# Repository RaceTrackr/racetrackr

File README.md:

# racetrackr
A repository for the student-led development of Racetrackr - An asset used for tracking data, both in the pits and on raceday at greenpower racing events.
This repository is happy for any help you are willing to give :)

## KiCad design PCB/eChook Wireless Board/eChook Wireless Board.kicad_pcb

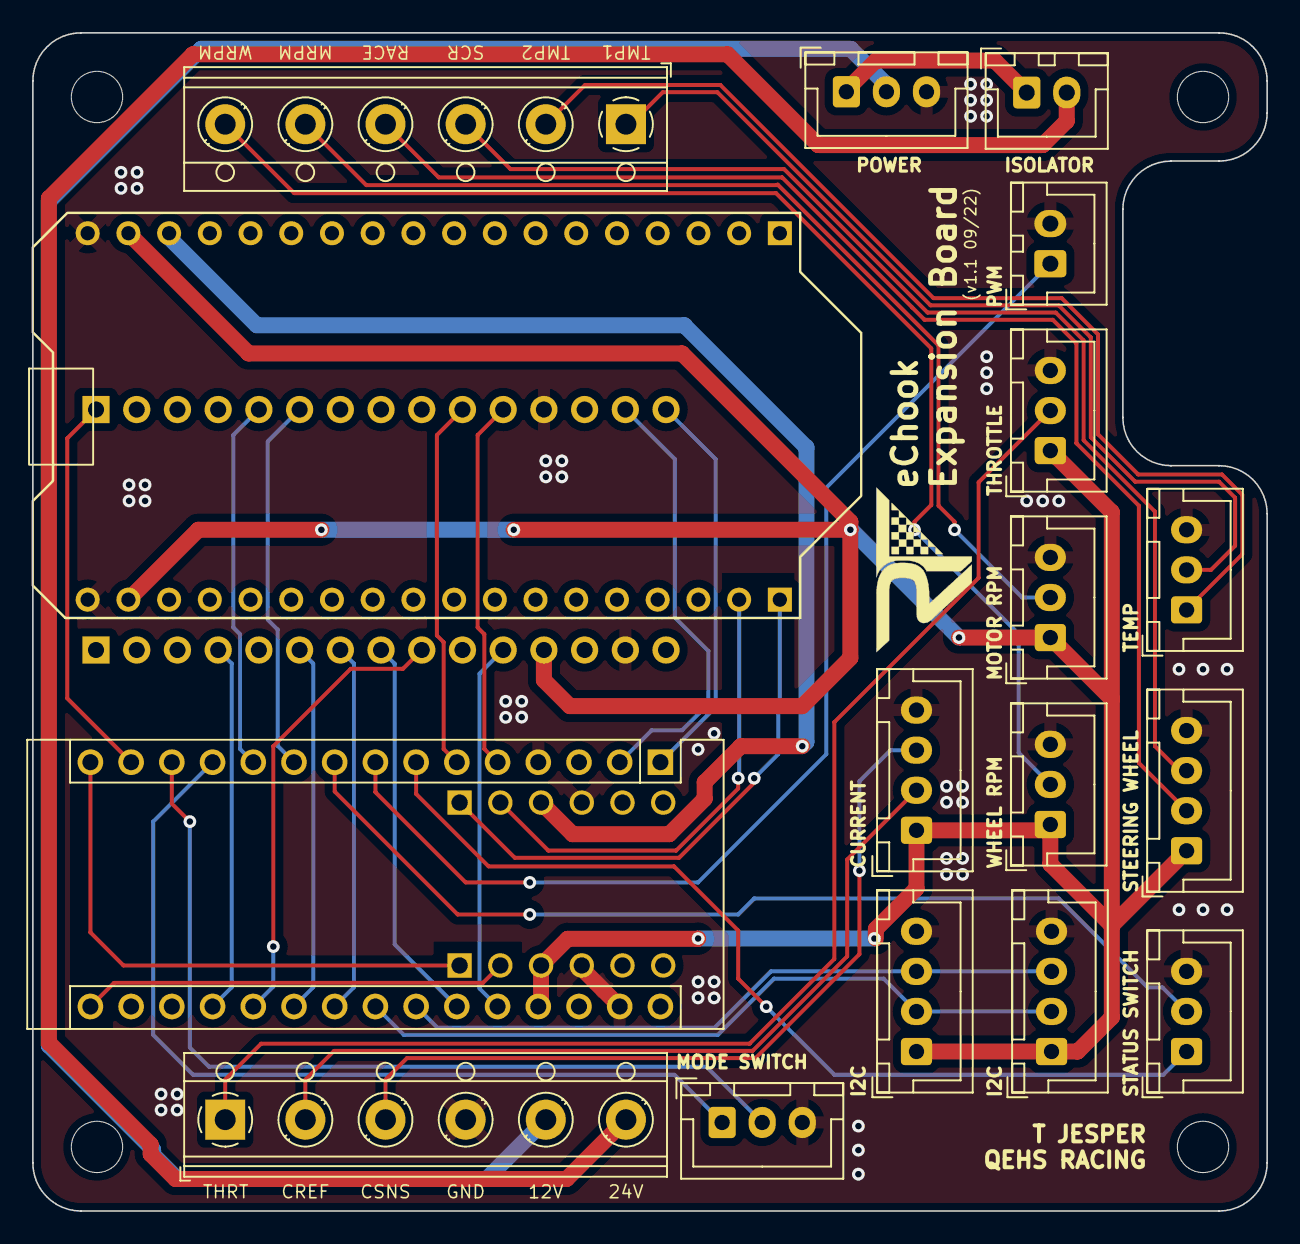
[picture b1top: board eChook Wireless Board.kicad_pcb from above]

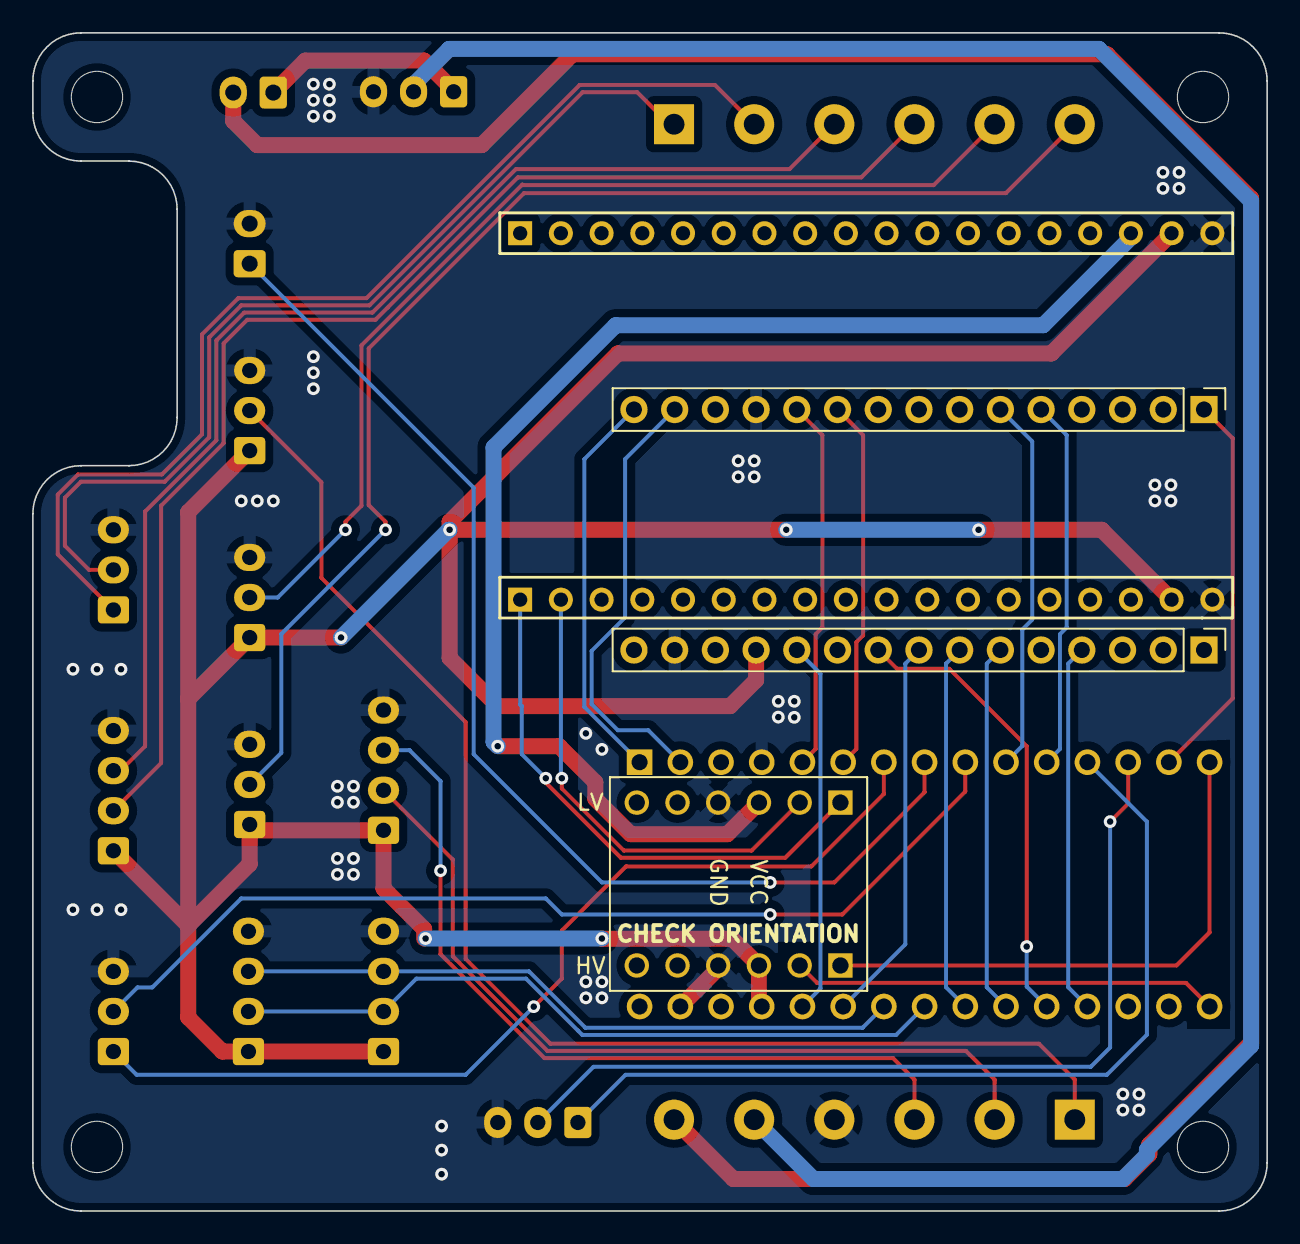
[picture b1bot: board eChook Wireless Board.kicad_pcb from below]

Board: 2 copper layers, 77.0 x 73.5 mm, 24 parts (3 on the bottom side), 39 nets.

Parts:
A: MountingHole_3.2mm_M3
A1: Arduino_Nano_v3.x; Arduino_Nano
B: MountingHole_3.2mm_M3
C: MountingHole_3.2mm_M3
D: MountingHole_3.2mm_M3
J1: POWER_CONNECTION; JST_XH_B3B-XH-A_1x03_P2.50mm_Vertical
J2: POWER_SWITCH; JST_XH_B2B-XH-A_1x02_P2.50mm_Vertical
J3: PWM_OUTPUT_CONN; JST_XH_B2B-XH-A_1x02_P2.50mm_Vertical
J4, J7: Conn_01x15_Male; PinHeader_1x15_P2.54mm_Vertical
J5: THROTTLE_CONNECTION; JST_XH_B3B-XH-A_1x03_P2.50mm_Vertical
J6: I2C_1_CONN; JST_XH_B4B-XH-A_1x04_P2.50mm_Vertical
J8: I2C_2_CONN; JST_XH_B4B-XH-A_1x04_P2.50mm_Vertical
J9: MOTOR_RPM_CONNECTION; JST_XH_B3B-XH-A_1x03_P2.50mm_Vertical
J10: WHEEL_RPM_CONNECTION; JST_XH_B3B-XH-A_1x03_P2.50mm_Vertical
J12, J18: STATUS_CONNECTION; JST_XH_B3B-XH-A_1x03_P2.50mm_Vertical
J13: CURRENT_CONN; JST_XH_B4B-XH-A_1x04_P2.50mm_Vertical
J14: TEMP_CONNECTION; JST_XH_B3B-XH-A_1x03_P2.50mm_Vertical
J15: WHEEL_CONN; JST_XH_B4B-XH-A_1x04_P2.50mm_Vertical
J16, J17: Screw_Terminal_01x06; TerminalBlock_RND_205-00016_1x06_P5.00mm_Horizontal
U1: LogicLevelConverter; CONV_BOB-12009
U2: ESP32_LoRa; ESP32 LoRa

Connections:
12_B2B: J1.2, J16.5
24_B2B: J2.2, J16.6
+3V3: U1.LV, U2.16 (3V3)
+5V: A1.27 (+5V), J4.12, J5.1, J6.1, J8.1, J9.1, J10.1, J13.1, J15.1, U1.HV, U2.17 (5V), U2.20 (5V)
/+24V_ISOLATED: J1.1, J2.1
BATT_1: A1.26 (A7), J4.11
BATT_T: A1.19 (A0), J4.4
BRAKE: A1.10 (D7), J7.6
BT_IN: A1.2 (D0/RX), J7.14
BT_OUT: A1.1 (D1/TX), J7.15
CREF_B2B: J13.2, J16.2
CSENSE_B2B: J13.3, J16.3
CURRENT: A1.21 (A2), J4.6
GND: A1.4 (GND), A1.29 (GND), J1.3, J3.2, J4.14, J5.3, J6.4, J7.12, J8.4, J9.3, J10.3, J12.3, J13.4, J14.3, J15.4, J16.4, J18.3, U1.GND_1 (GND), U1.GND_2 (GND), U2.18 (GND), U2.19 (GND)
MODE_INPUT_1: A1.12 (D9), J18.1
MODE_INPUT_2: A1.13 (D10), J18.2
MOTOR_PWM: A1.8 (D5), J3.1
MOTOR_RPM: A1.5 (D2), J7.11
MRPM_B2B: J9.2, J17.5
RACE_START: A1.11 (D8), J7.5
RACE_START_B2B: J15.2, J17.4
RACE_SWITCH: A1.7 (D4), J12.1
RX_HIGH: A1.16 (D13), U1.HV2
RX_LOW: U1.LV1, U2.36 (GPIO16)
SCL: A1.24 (A5), J6.3, J8.3
SCREEN_SWITCH: A1.14 (D11), J7.1
SCREEN_SWITCH_B2B: J15.3, J17.3
SDA: A1.23 (A4), J6.2, J8.2
TELEMETRY_SWITCH: A1.9 (D6), J12.2
TEMP1_B2B: J14.1, J17.2
TEMP2_B2B: J14.2, J17.1
TEMP_1: A1.20 (A1), J4.9
TEMP_2: A1.25 (A6), J4.8
THROTTLE: A1.22 (A3), J4.7
THROTTLE_B2B: J5.2, J16.1
TX_HIGH: A1.15 (D12), U1.HV1
TX_LOW: U1.LV2, U2.35 (GPIO17)
WHEEL_RPM: A1.6 (D3), J7.10
WRPM_B2B: J10.2, J17.6

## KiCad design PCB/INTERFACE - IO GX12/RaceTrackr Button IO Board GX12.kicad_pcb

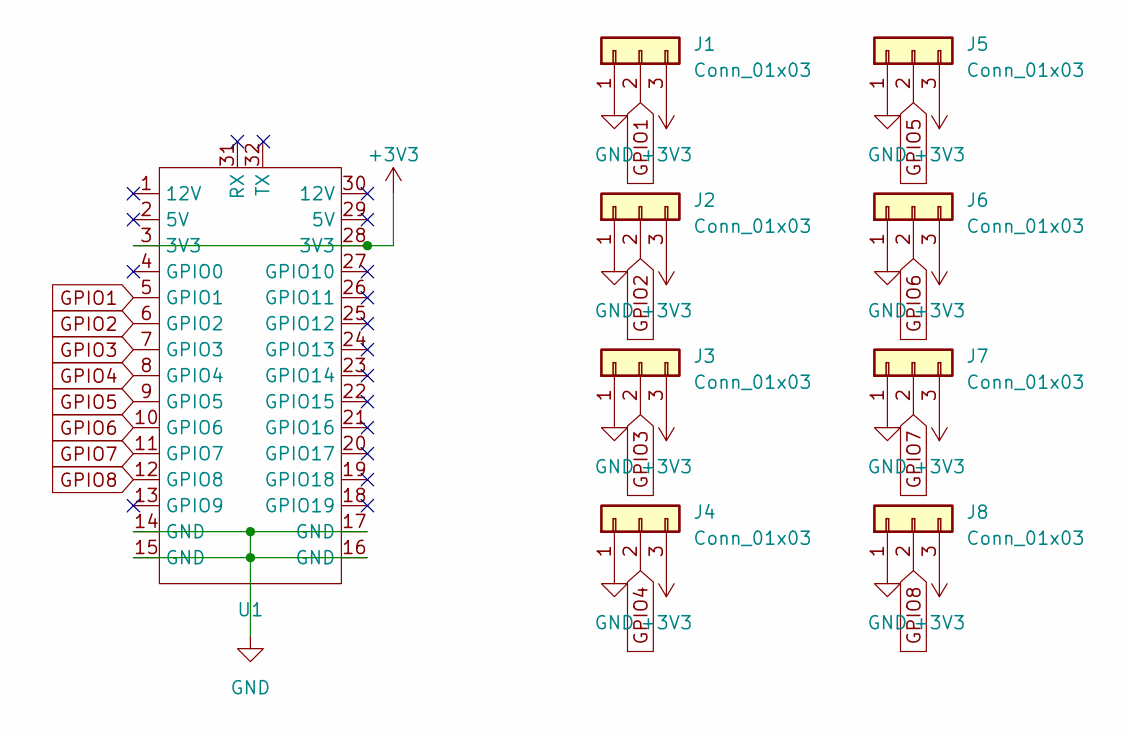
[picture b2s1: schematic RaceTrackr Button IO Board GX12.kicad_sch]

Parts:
J1, J2, J3, J4, J5, J6, J7, J8: Conn_01x03; GX12-3
U1: RaceTrackr Interface Board Reference

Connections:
+3V3: J1.3, J2.3, J3.3, J4.3, J5.3, J6.3, J7.3, J8.3, U1.3 (3V3), U1.28 (3V3)
GND: J1.1, J2.1, J3.1, J4.1, J5.1, J6.1, J7.1, J8.1, U1.14 (GND), U1.15 (GND), U1.16 (GND), U1.17 (GND)
GPIO1: J1.2, U1.5 (GPIO1)
GPIO2: J2.2, U1.6 (GPIO2)
GPIO3: J3.2, U1.7 (GPIO3)
GPIO4: J4.2, U1.8 (GPIO4)
GPIO5: J5.2, U1.9 (GPIO5)
GPIO6: J6.2, U1.10 (GPIO6)
GPIO7: J7.2, U1.11 (GPIO7)
GPIO8: J8.2, U1.12 (GPIO8)

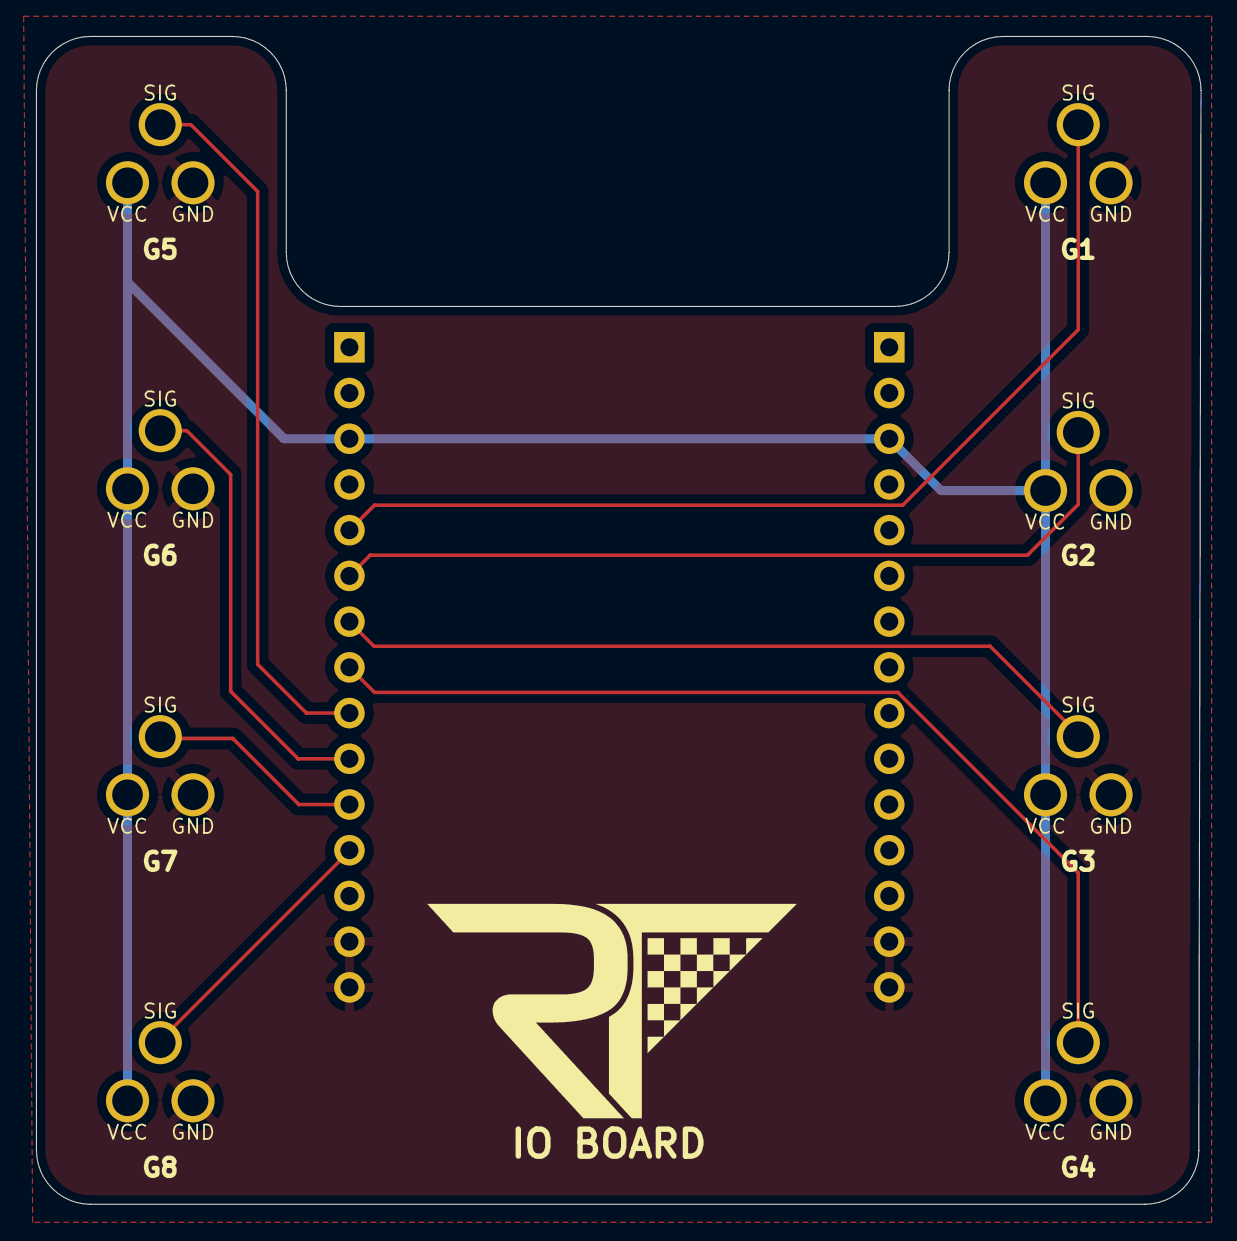
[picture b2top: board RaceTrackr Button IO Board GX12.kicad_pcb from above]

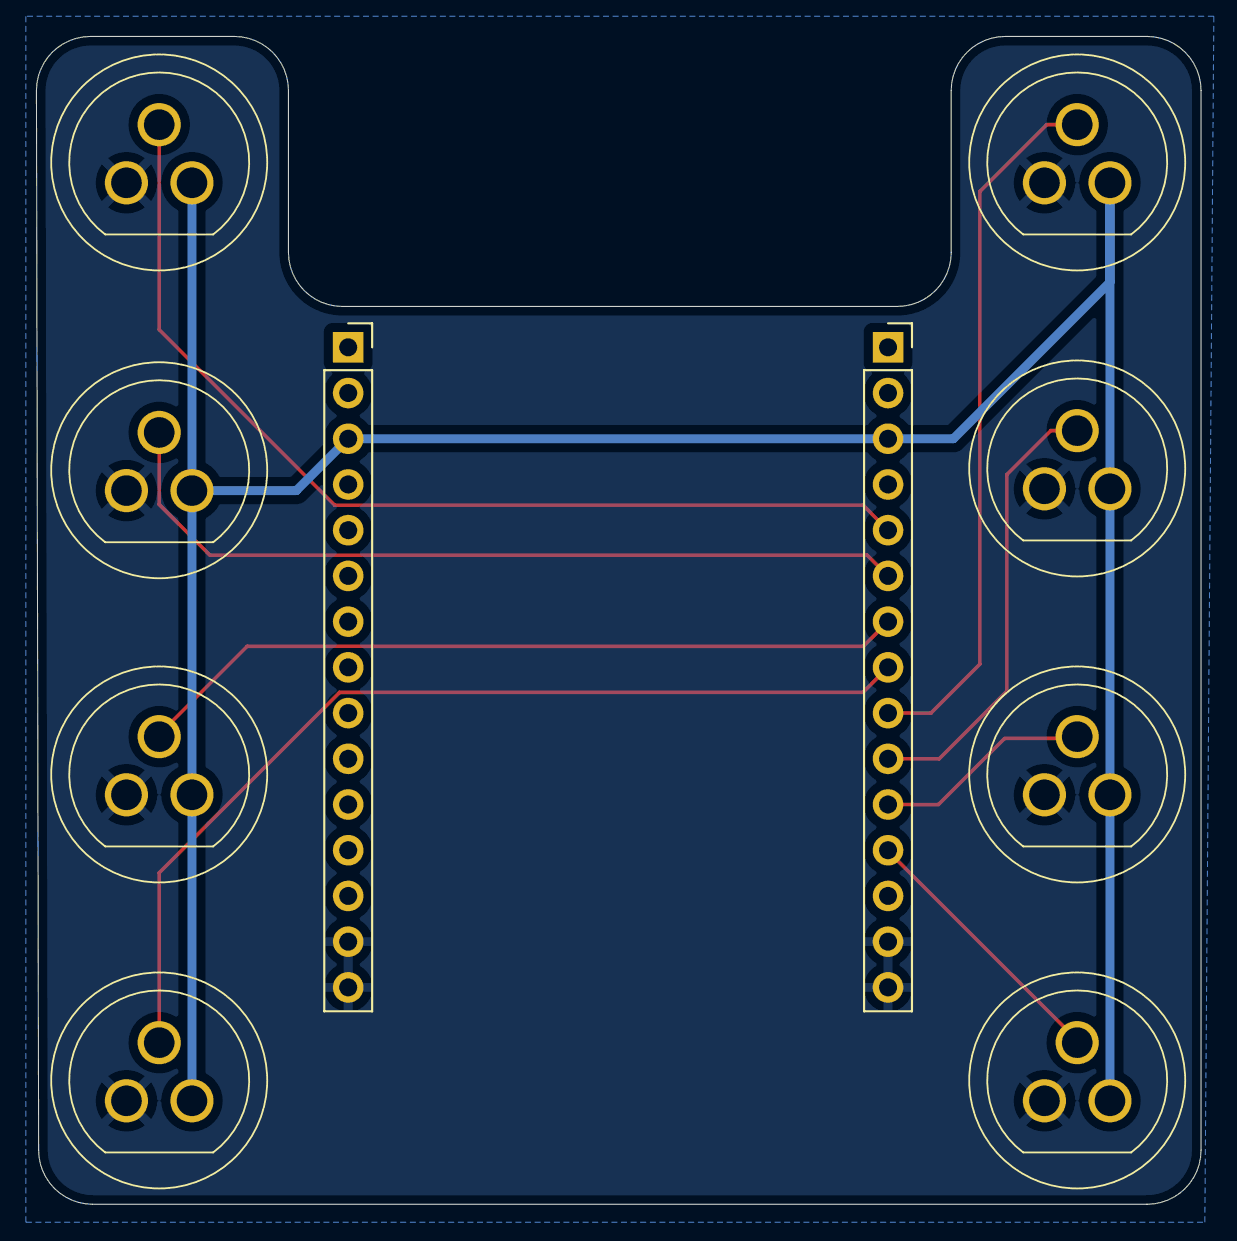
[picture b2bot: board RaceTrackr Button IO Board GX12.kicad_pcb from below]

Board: 2 copper layers, 64.7 x 64.9 mm, 9 parts (8 on the bottom side), 10 nets.

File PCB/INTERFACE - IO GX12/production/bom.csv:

Designator,Footprint,Quantity,Value,LCSC Part #
"J1, J2, J3, J4, J5, J6, J7, J8",GX12-3_NOSS,8,Conn_01x03,
U1,RaceTrackr Interface Board Reference,1,~,

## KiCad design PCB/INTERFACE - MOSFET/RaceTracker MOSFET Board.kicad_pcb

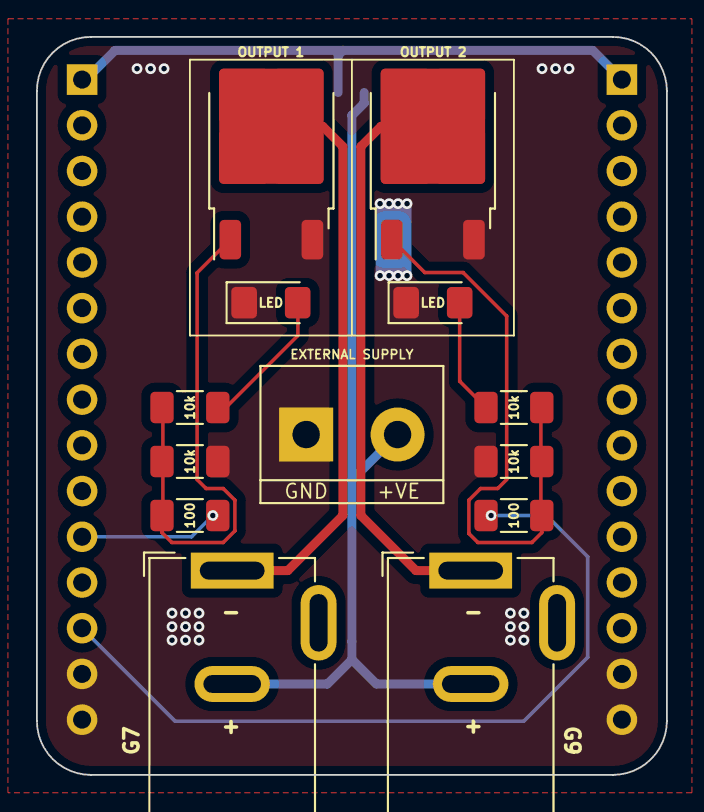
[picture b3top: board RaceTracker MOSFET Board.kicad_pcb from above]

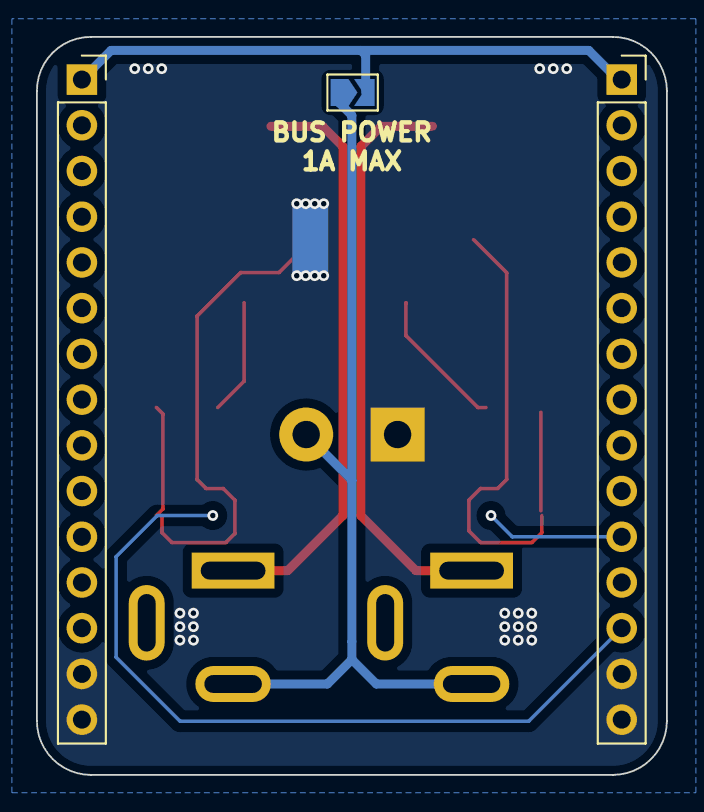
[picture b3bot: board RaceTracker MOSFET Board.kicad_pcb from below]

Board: 2 copper layers, 35.0 x 41.0 mm, 16 parts (3 on the bottom side), 13 nets.

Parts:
BUS POWER: BUS POWER; SolderJumper-2_P1.3mm_Open_TrianglePad1.0x1.5mm
D1, D2: LED; LED_1206_3216Metric_Pad1.42x1.75mm_HandSolder
J1: CON_L; PinSocket_1x15_P2.54mm_Vertical
J2: CON_R; PinSocket_1x15_P2.54mm_Vertical
J3: DC IN; TerminalBlock_bornier-2_P5.08mm
J6: OUTPUT 1; BarrelJack_GCT_DCJ200-10-A_Horizontal
J7: OUTPUT 2; BarrelJack_GCT_DCJ200-10-A_Horizontal
OUTPUT 1, OUTPUT 2: IRF540N; TO-252-2
R1, R4: 100; R_1206_3216Metric_Pad1.30x1.75mm_HandSolder
R2, R3, R5, R6: 10k; R_1206_3216Metric_Pad1.30x1.75mm_HandSolder

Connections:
+3V3: J1.3, J2.3
+5V: J1.2, J2.2
+12V: BUS POWER.2 (B), J1.1, J2.1
+24V: BUS POWER.1 (A), J3.2, J6.2, J7.2
FET_1_Trigger: J1.11, R1.1
FET_2_Trigger: J1.13, R4.1
GND: D1.1 (K), D2.1 (K), J1.14, J1.15, J2.14, J2.15, J3.1, OUTPUT 1.3 (S), OUTPUT 2.3 (S), R2.1, R5.1
unnamed: D1.2 (A), R3.1
unnamed: D2.2 (A), R6.1
unnamed: OUTPUT 1.1 (G), R1.2, R2.2, R3.2
unnamed: OUTPUT 2.1 (G), R4.2, R5.2, R6.2
OUTPUT_1: J6.1, OUTPUT 1.2 (D)
OUTPUT_2: J7.1, OUTPUT 2.2 (D)

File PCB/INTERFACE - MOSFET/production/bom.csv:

Designator,Footprint,Quantity,Value,LCSC Part #
BUS POWER,SolderJumper-2_P1.3mm_Open_TrianglePad1.0x1.5mm,1,BUS POWER,
J1,PinSocket_1x15_P2.54mm_Vertical,1,CON_L,
J2,PinSocket_1x15_P2.54mm_Vertical,1,CON_R,
J3,TerminalBlock_bornier-2_P5.08mm,1,DC IN,
J6,BarrelJack_GCT_DCJ200-10-A_Horizontal,1,OUTPUT 1,
J7,BarrelJack_GCT_DCJ200-10-A_Horizontal,1,OUTPUT 2,
"OUTPUT 1, OUTPUT 2",TO-252-2,2,IRF540N,
"R1, R4",1206,2,100,
"R2, R3, R5, R6",1206,4,10k,

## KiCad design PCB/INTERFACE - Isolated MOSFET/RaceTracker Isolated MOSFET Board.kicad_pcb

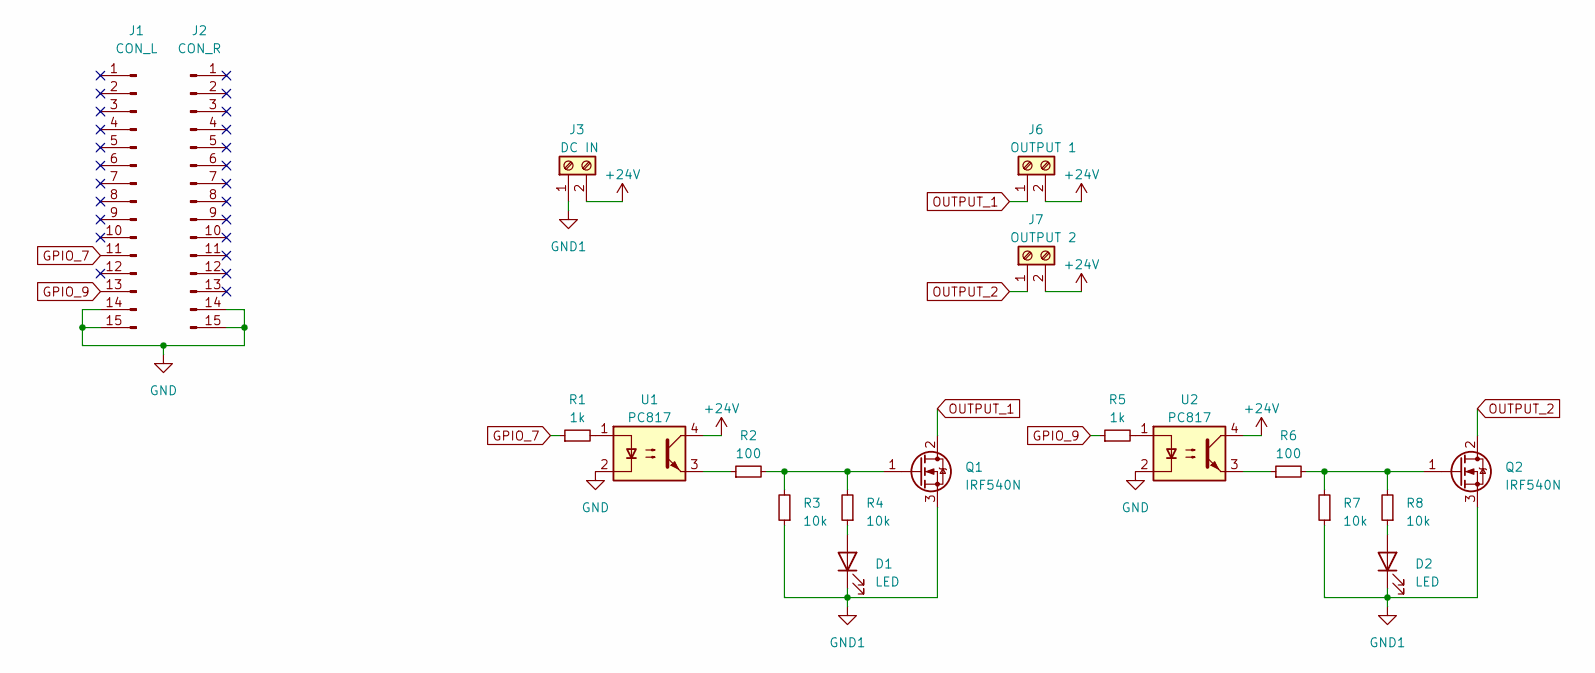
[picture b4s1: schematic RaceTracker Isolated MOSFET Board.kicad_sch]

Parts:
D1, D2: LED; LED_1206_3216Metric_Pad1.42x1.75mm_HandSolder; LCSC C84256
J1: CON_L; PinSocket_1x15_P2.54mm_Vertical
J2: CON_R; PinSocket_1x15_P2.54mm_Vertical
J3: DC IN; TerminalBlock_bornier-2_P5.08mm
J6: OUTPUT 1; BarrelJack_GCT_DCJ200-10-A_Horizontal
J7: OUTPUT 2; BarrelJack_GCT_DCJ200-10-A_Horizontal
Q1, Q2: IRF540N; TO-252-2
R1, R5: 1k; R_1206_3216Metric_Pad1.30x1.75mm_HandSolder
R2, R6: 100; R_1206_3216Metric_Pad1.30x1.75mm_HandSolder
R3, R4, R7, R8: 10k; R_1206_3216Metric_Pad1.30x1.75mm_HandSolder
U1, U2: PC817; DIP-4_W7.62mm

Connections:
+24V: J3.2, J6.2, J7.2, U1.4, U2.4
GND: J1.14, J1.15, J2.14, J2.15, U1.2, U2.2
GND1: D1.1 (K), D2.1 (K), J3.1, Q1.3 (S), Q2.3 (S), R3.1, R7.1
GPIO_7: J1.11, R1.1
GPIO_9: J1.13, R5.1
unnamed: D1.2 (A), R4.1
unnamed: D2.2 (A), R8.1
unnamed: Q1.1 (G), R2.2, R3.2, R4.2
unnamed: Q2.1 (G), R6.2, R7.2, R8.2
unnamed: R1.2, U1.1
unnamed: R2.1, U1.3
unnamed: R5.2, U2.1
unnamed: R6.1, U2.3
OUTPUT_1: J6.1, Q1.2 (D)
OUTPUT_2: J7.1, Q2.2 (D)

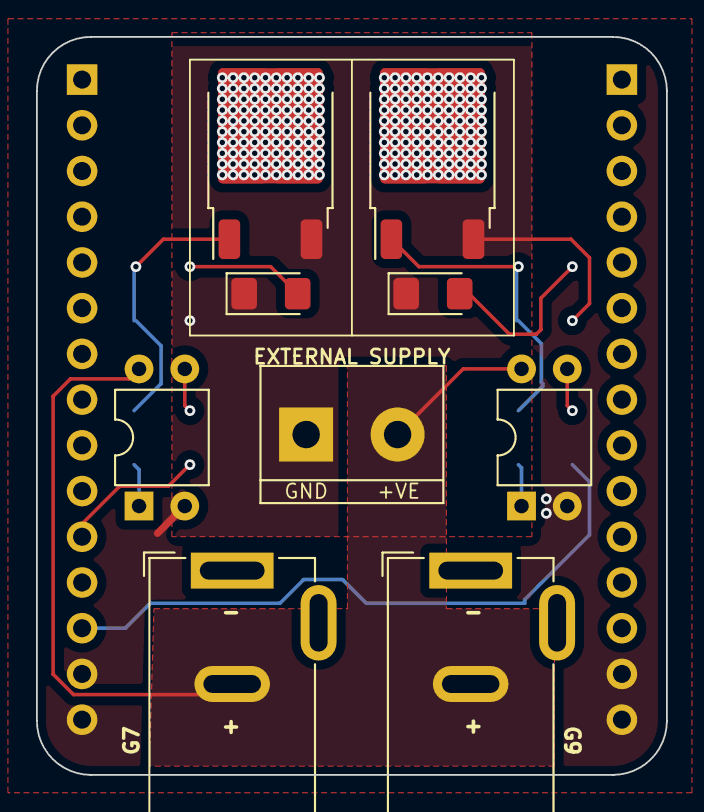
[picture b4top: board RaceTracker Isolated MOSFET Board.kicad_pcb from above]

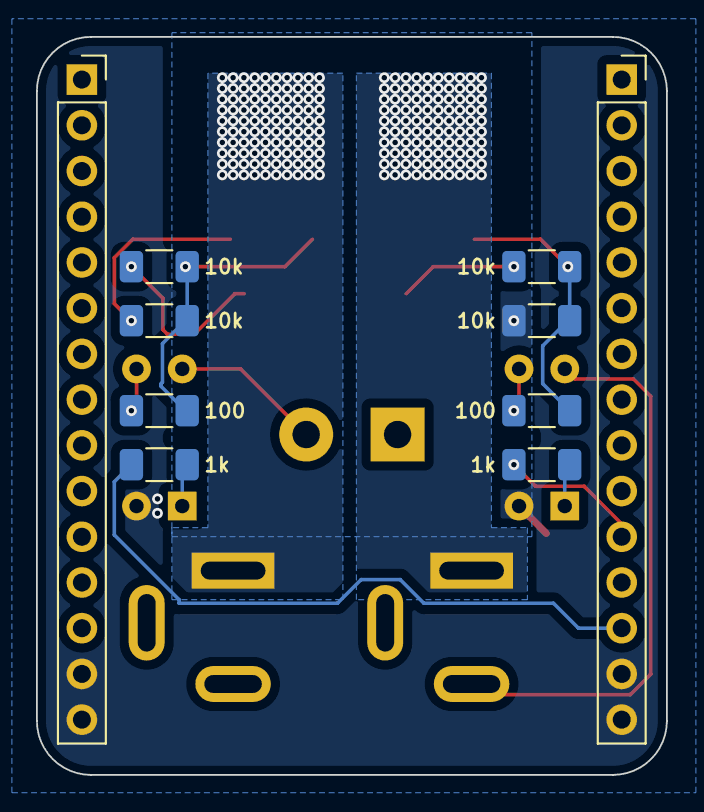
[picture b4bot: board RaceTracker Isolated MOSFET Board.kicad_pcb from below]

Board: 2 copper layers, 35.0 x 41.0 mm, 19 parts (10 on the bottom side), 15 nets.

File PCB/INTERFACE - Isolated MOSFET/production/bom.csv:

Designator,Footprint,Quantity,Value,LCSC Part #
J1,PinSocket_1x15_P2.54mm_Vertical,1,CON_L,
J2,PinSocket_1x15_P2.54mm_Vertical,1,CON_R,
J3,TerminalBlock_bornier-2_P5.08mm,1,DC IN,
J6,BarrelJack_GCT_DCJ200-10-A_Horizontal,1,OUTPUT 1,
J7,BarrelJack_GCT_DCJ200-10-A_Horizontal,1,OUTPUT 2,
"Q1, Q2",TO-252-2,2,IRF540N,
"R1, R5",1206,2,1k,
"R2, R6",1206,2,100,
"R3, R4, R7, R8",1206,4,10k,
"U1, U2",DIP-4_W7.62mm,2,PC817,

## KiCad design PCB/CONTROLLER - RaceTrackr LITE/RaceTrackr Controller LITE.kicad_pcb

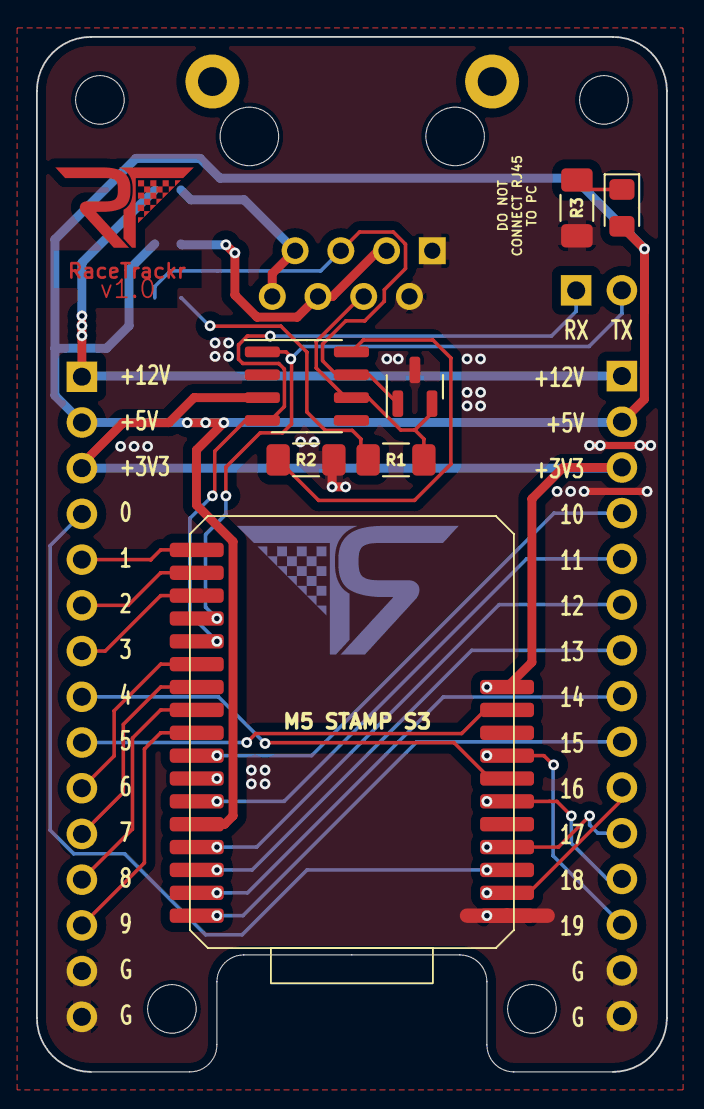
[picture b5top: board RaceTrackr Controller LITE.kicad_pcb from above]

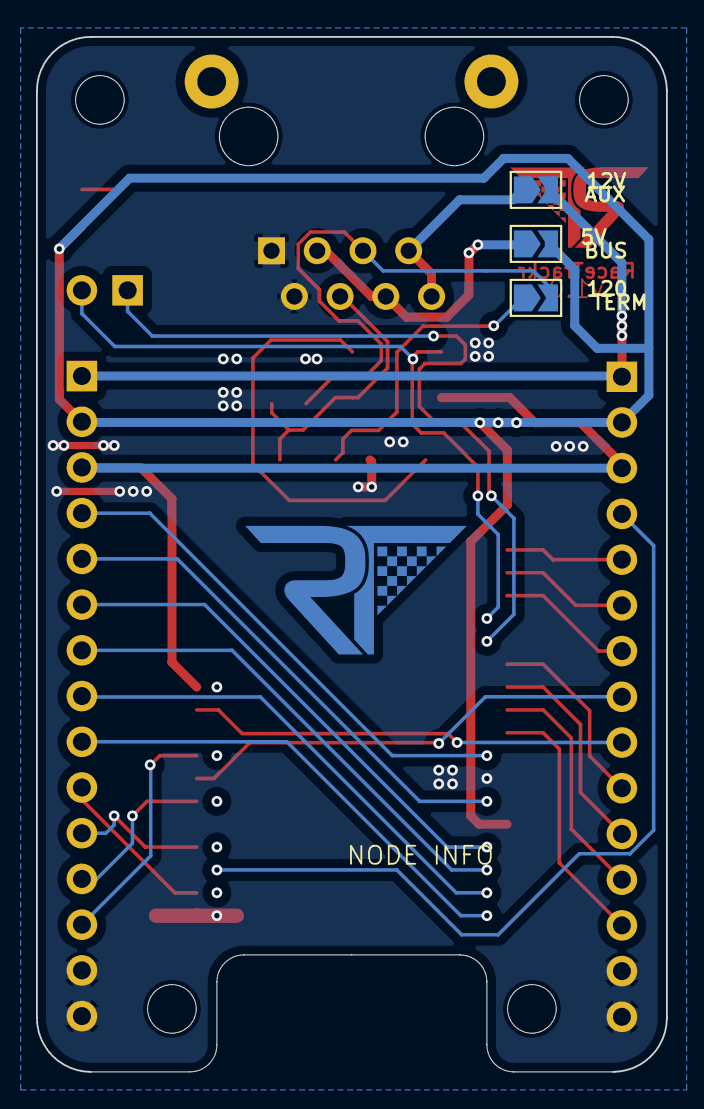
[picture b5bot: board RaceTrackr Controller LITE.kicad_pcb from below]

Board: 2 copper layers, 35.0 x 57.5 mm, 18 parts (3 on the bottom side), 33 nets.

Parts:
D4: LED; LED_0805_2012Metric_Pad1.15x1.40mm_HandSolder
J1, J2: CON_L; PinHeader_1x15_P2.54mm_Vertical
J3: Conn_01x02_Pin; PinHeader_1x02_P2.54mm_Vertical
J5: RJ45; RJ45_Ninigi_GE
JP1, JP2, JP3: Jumper; SolderJumper-2_P1.3mm_Open_TrianglePad1.0x1.5mm
MOUNT_L: MountingHole_2.7mm_M2.5_DIN965
MOUNT_L#2, MOUNT_L#3: MountingHole_2.7mm_M2.5_DIN965
MOUNT_R: MountingHole_2.7mm_M2.5_DIN965
R1: 120; R_1206_3216Metric_Pad1.30x1.75mm_HandSolder
R2, R3: 10k; R_1206_3216Metric_Pad1.30x1.75mm_HandSolder
U1: M5_Stamp_S3; M5StampS3
U3: ESD2CAN24-Q1; SOT-23
U4: SN65HVD230; SOIC-8_3.9x4.9mm_P1.27mm

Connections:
+3V3: J1.3, J2.3, U1.28 (3V3), U4.3 (VCC)
+5V: D4.2 (A), J1.2, J2.2, JP2.2 (B), U1.13 (5V)
CAN_H: J5.5, JP1.2 (B), U3.1 (H), U4.7 (CANH)
CAN_L: J5.4, R1.2, U3.2 (L), U4.6 (CANL)
CAN_RX: J3.1, U1.5 (GPIO_5), U4.4 (R)
CAN_TX: J3.2, U1.4 (GPIO_4), U4.1 (D)
GND: J1.14, J1.15, J2.14, J2.15, J5.1, J5.2, R2.2, R3.2, U1.11 (GND), U1.18 (GND), U3.3 (GND), U4.2 (GND)
GPIO_0: J2.4, U1.20 (GPIO_0)
GPIO_1: J2.5, U1.1 (GPIO_1)
GPIO_2: J2.6, U1.2 (GPIO_2)
GPIO_3: J2.7, U1.3 (GPIO_3)
GPIO_4: J2.8, U1.24 (GPIO_44)
GPIO_5: J2.9, U1.27 (GPIO_46)
GPIO_6: J2.10, U1.6 (GPIO_6)
GPIO_7: J2.11, U1.7 (GPIO_7)
GPIO_8: J2.12, U1.8 (GPIO_8)
GPIO_9: J2.13, U1.9 (GPIO_9)
GPIO_10: J1.4, U1.10 (GPIO_10)
GPIO_11: J1.5, U1.12 (GPIO_11)
GPIO_12: J1.6, U1.14 (GPIO_12)
GPIO_13: J1.7, U1.15 (GPIO_13)
GPIO_14: J1.8, U1.16 (GPIO_14)
GPIO_15: J1.9, U1.17 (GPIO_15)
GPIO_16: J1.10, U1.19 (GPIO_39)
GPIO_17: J1.11, U1.21 (GPIO_40)
GPIO_18: J1.12, U1.23 (GPIO_41)
GPIO_19: J1.13, U1.25 (GPIO_42)
unnamed: D4.1 (K), R3.1
unnamed: J1.1, J2.1, JP3.2 (B)
unnamed: JP1.1 (A), R1.1
unnamed: J5.3, J5.6, JP2.1 (A)
unnamed: R2.1, U4.8 (Rs)
V_INPUT: J5.7, J5.8, JP3.1 (A)

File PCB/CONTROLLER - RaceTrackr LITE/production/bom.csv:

Designator,Footprint,Quantity,Value,LCSC Part #
D4,0805,1,LED,C84256
J3,PinHeader_1x02_P2.54mm_Vertical,1,Conn_01x02_Pin,
R1,1206,1,120,C17909
"R2, R3",1206,2,10k,C17902
U1,M5StampS3,1,M5_Stamp_S3,
U3,SOT-23,1,ESD2CAN24-Q1,C907830
U4,SOIC-8_3.9x4.9mm_P1.27mm,1,SN65HVD230,C12084

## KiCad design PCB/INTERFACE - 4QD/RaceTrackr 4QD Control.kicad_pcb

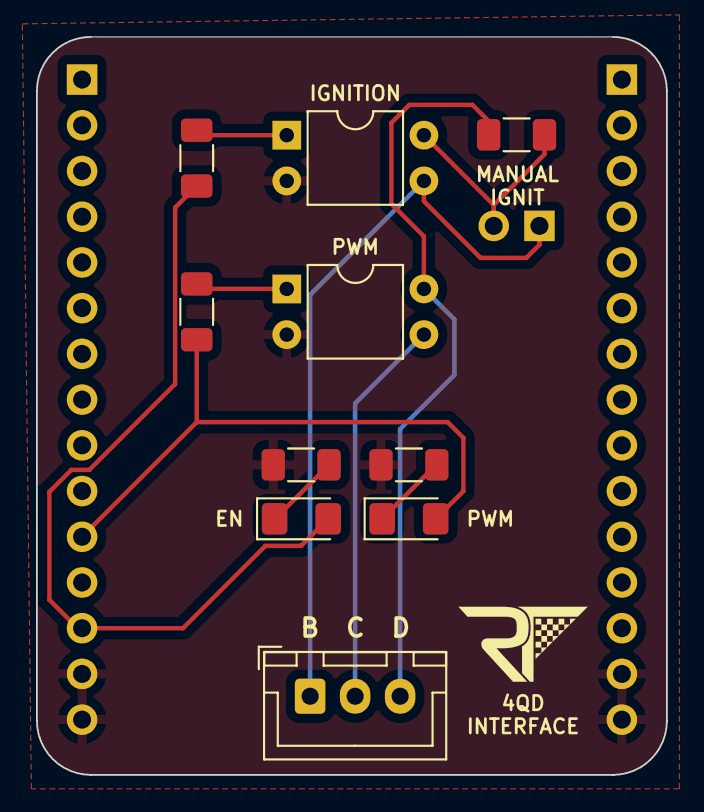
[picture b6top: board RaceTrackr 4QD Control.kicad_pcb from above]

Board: 2 copper layers, 35.0 x 41.0 mm, 12 parts (0 on the bottom side), 11 nets.

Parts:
D1, D2: RED; LED_1206_3216Metric_Pad1.42x1.75mm_HandSolder
IGNITION: PC817; DIP-4_W7.62mm
J3: IGNITION SWITCH; PinHeader_1x02_P2.54mm_Horizontal
J4: Conn_01x03_Pin; JST_XH_B3B-XH-A_1x03_P2.50mm_Vertical
PWM: PC817; DIP-4_W7.62mm
R1, R2: 1k; R_1206_3216Metric_Pad1.30x1.75mm_HandSolder
R3, R4, R5: 10k; R_1206_3216Metric_Pad1.30x1.75mm_HandSolder
U3: RaceTrackr Interface Board Reference

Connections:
/B: IGNITION.3, J3.1, J4.1
/C: J4.2, PWM.3
/D: J4.3, PWM.4, R3.1
EN: D2.2 (A), R1.1, U3.13 (GPIO9)
GND: IGNITION.2, PWM.2, R4.1, R5.1, U3.14 (GND), U3.15 (GND), U3.16 (GND), U3.17 (GND)
unnamed: D1.1 (K), R4.2
unnamed: D2.1 (K), R5.2
unnamed: IGNITION.4, J3.2, R3.2
unnamed: IGNITION.1, R1.2
unnamed: PWM.1, R2.2
PWM: D1.2 (A), R2.1, U3.11 (GPIO7)

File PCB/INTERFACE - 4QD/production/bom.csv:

Designator,Footprint,Quantity,Value,LCSC Part #
"D1, D2",1206,2,RED,
"IGNITION, PWM",DIP-4_W7.62mm,2,PC817,
J3,PinHeader_1x02_P2.54mm_Horizontal,1,IGNITION SWITCH,
J4,JST_XH_B3B-XH-A_1x03_P2.50mm_Vertical,1,Conn_01x03_Pin,
"R1, R2",1206,2,1k,
"R3, R4, R5",1206,3,10k,
U3,RaceTrackr Interface Board Reference,1,~,

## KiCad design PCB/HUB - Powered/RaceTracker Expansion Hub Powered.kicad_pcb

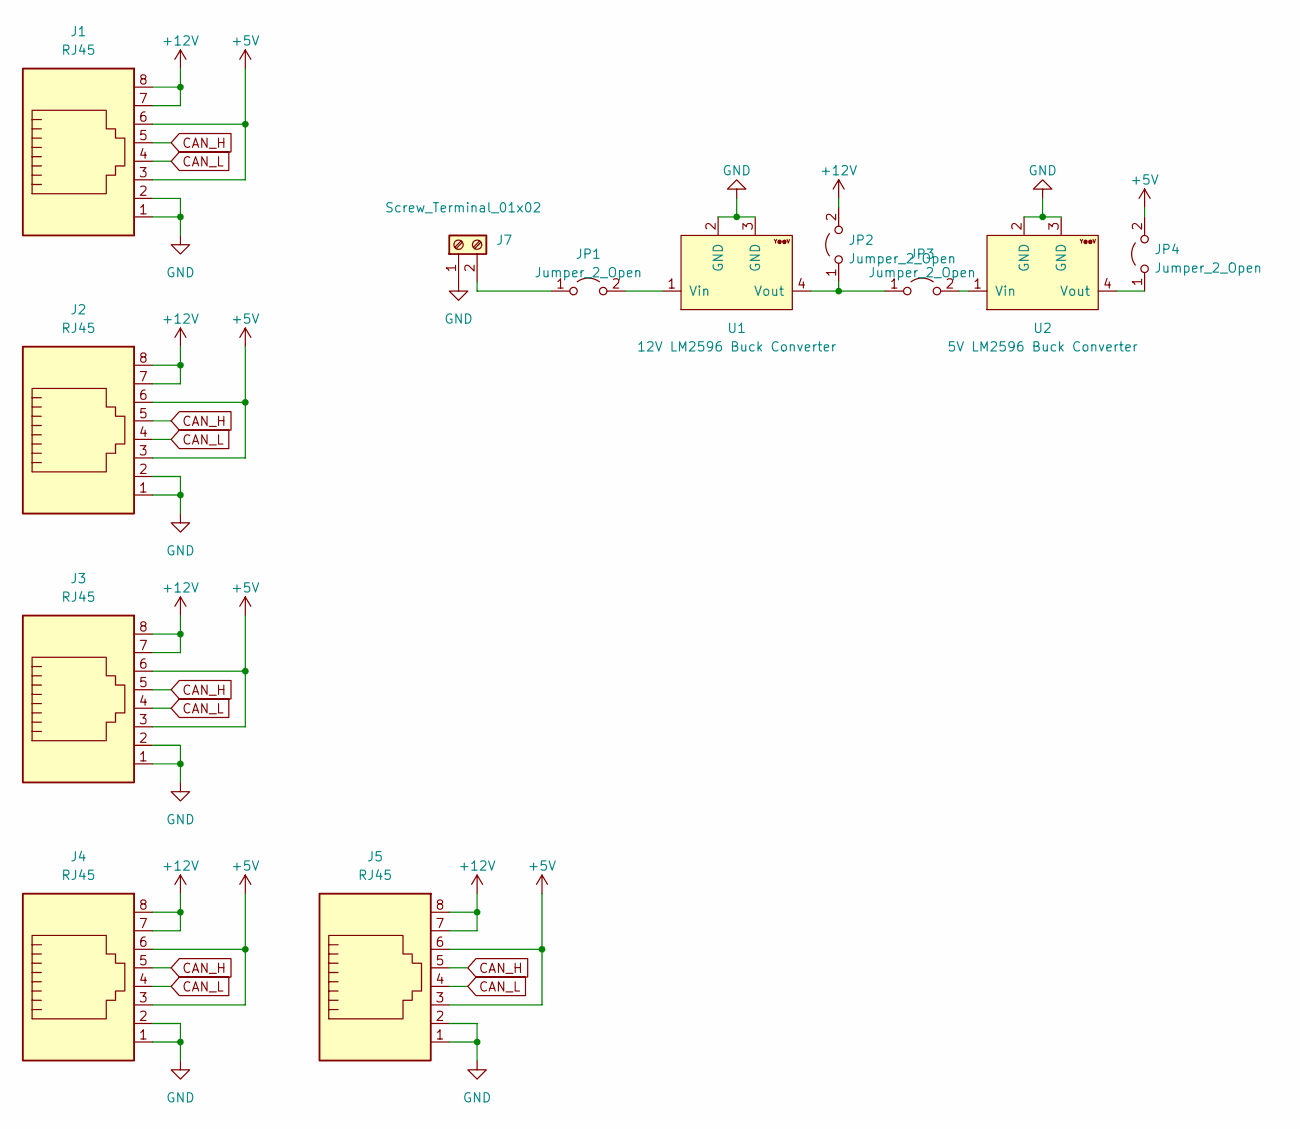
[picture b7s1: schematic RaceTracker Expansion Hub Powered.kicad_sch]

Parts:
J1, J2, J3, J4, J5: RJ45; RJ45_Ninigi_GE
J7: Screw_Terminal_01x02; TerminalBlock_bornier-2_P5.08mm
JP1, JP2, JP3, JP4: Jumper_2_Open; PinHeader_1x02_P2.54mm_Vertical
U1: 12V LM2596 Buck Converter; LM2596 Buck Converter
U2: 5V LM2596 Buck Converter; LM2596 Buck Converter

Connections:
+5V: J1.3, J1.6, J2.3, J2.6, J3.3, J3.6, J4.3, J4.6, J5.3, J5.6, JP4.2 (B)
+12V: J1.7, J1.8, J2.7, J2.8, J3.7, J3.8, J4.7, J4.8, J5.7, J5.8, JP2.2 (B)
CAN_H: J1.5, J2.5, J3.5, J4.5, J5.5
CAN_L: J1.4, J2.4, J3.4, J4.4, J5.4
GND: J1.1, J1.2, J2.1, J2.2, J3.1, J3.2, J4.1, J4.2, J5.1, J5.2, J7.1, U1.2 (GND), U1.3 (GND), U2.2 (GND), U2.3 (GND)
unnamed: J7.2, JP1.1 (A)
unnamed: JP1.2 (B), U1.1 (Vin)
unnamed: JP2.1 (A), JP3.1 (A), U1.4 (Vout)
unnamed: JP3.2 (B), U2.1 (Vin)
unnamed: JP4.1 (A), U2.4 (Vout)

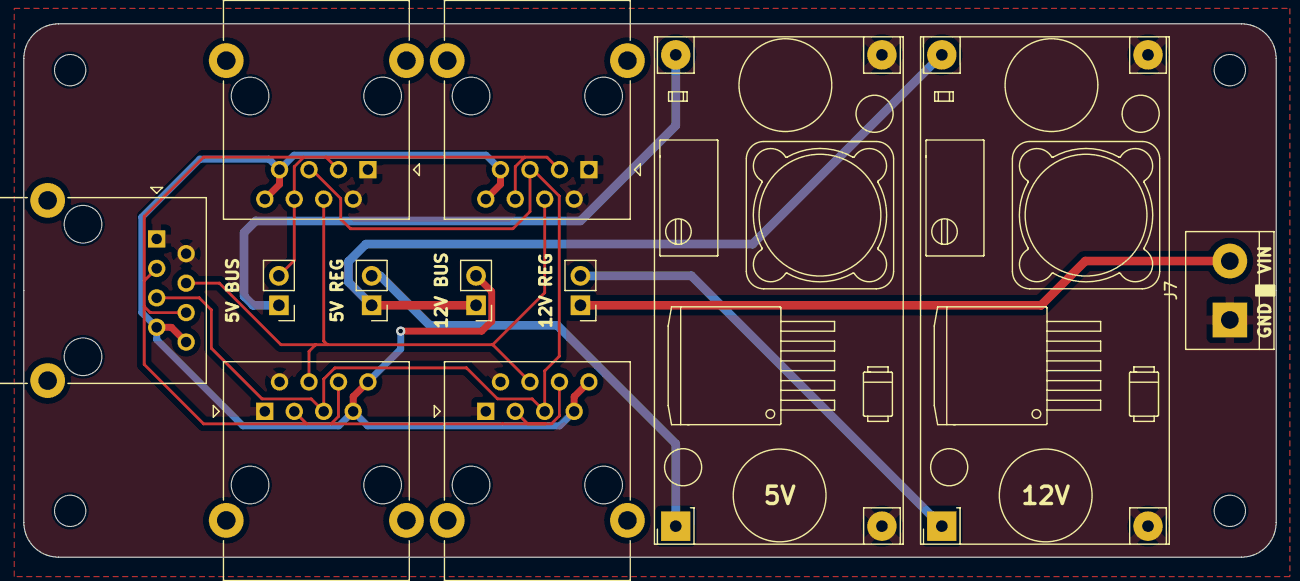
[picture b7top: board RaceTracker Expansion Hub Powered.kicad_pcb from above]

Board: 2 copper layers, 108.0 x 46.0 mm, 12 parts (0 on the bottom side), 10 nets.

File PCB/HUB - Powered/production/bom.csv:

Designator,Footprint,Quantity,Value,LCSC Part #
J7,TerminalBlock_bornier-2_P5.08mm,1,Screw_Terminal_01x02,
"JP1, JP2, JP3, JP4",PinHeader_1x02_P2.54mm_Vertical,4,Jumper_2_Open,
U1,LM2596 Buck Converter,1,12V LM2596 Buck Converter,
U2,LM2596 Buck Converter,1,5V LM2596 Buck Converter,
